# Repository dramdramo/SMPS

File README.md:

# SMPS

Here is the branch where Omar will make changes to the main project

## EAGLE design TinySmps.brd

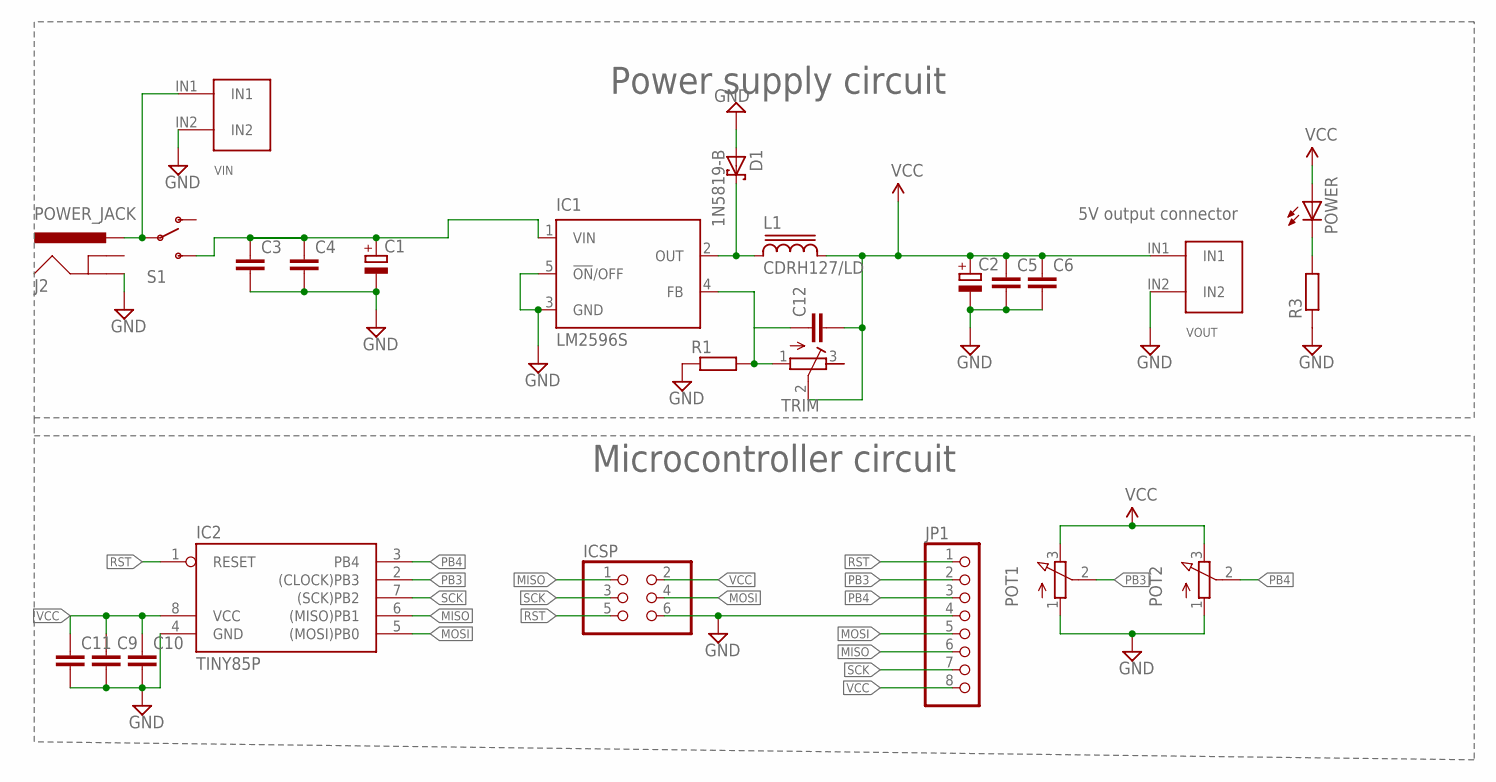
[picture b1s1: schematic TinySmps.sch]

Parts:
C1: CPOL-EUE7.5-16; E7,5-16
C2: CPOL-EUE5-10.5; E5-10,5
C3, C4, C5, C6, C9, C10, C11: C-EUC1206; C1206
C12: C2,5-3; C2.5-3
D1: 1N5819-B; DO41-7.6
IC1: LM2596S; TO263-5
IC2: TINY85P; DIL08
ICSP: PINHD-2X3; 2X03
J2: POWER_JACK; POWER_JACK_PTH
JP1: PINHD-1X8; 1X08
L1: CDRH127/LD
POT1, POT2: 3RP/1610N
POWER: LEDSML0805; SML0805
R1: R-EU_0204/7; 0204/7
R3: R-EU_R1206; R1206
S1: SWITCH-SPDTKIT; SWITCH-SPDT_KIT
TRIM: R-TRIMM3296W; RTRIM3296W
VIN: 1X2_5MM
VOUT: 1X2_5MM

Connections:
GND: C1.-, C2.-, C3.2, C4.2, C5.2, C6.2, C9.2, C10.2, C11.2, D1.A, IC1.3 (GND), IC1.5 (!ON!/OFF), IC2.4 (GND), ICSP.6, J2.GND, JP1.4, POT1.1 (A), POT2.1 (A), R1.1, R3.1, VIN.IN2, VOUT.IN2
IN: C1.+, C3.1, C4.1, IC1.1 (VIN), S1.3 (S)
MISO: IC2.6 ((MISO)PB1), ICSP.1, JP1.6
MOSI: IC2.5 ((MOSI)PB0), ICSP.4, JP1.5
unnamed: POWER.C, R3.2
unnamed: D1.C, IC1.2 (OUT), L1.1
unnamed: C12.1, IC1.4 (FB), R1.2, TRIM.1 (A)
unnamed: J2.PWR, S1.2, VIN.IN1
PB3: IC2.2 ((CLOCK)PB3), JP1.2, POT1.2 (S)
PB4: IC2.3 (PB4), JP1.3, POT2.2 (S)
RST: IC2.1 (RESET), ICSP.5, JP1.1
SCK: IC2.7 ((SCK)PB2), ICSP.3, JP1.7
VCC: C2.+, C5.1, C6.1, C9.1, C10.1, C11.1, C12.2, IC2.8 (VCC), ICSP.2, JP1.8, L1.2, POT1.3 (E), POT2.3 (E), POWER.A, TRIM.2 (S), VOUT.IN1

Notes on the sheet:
Power supply circuit
5V output connector
Microcontroller circuit

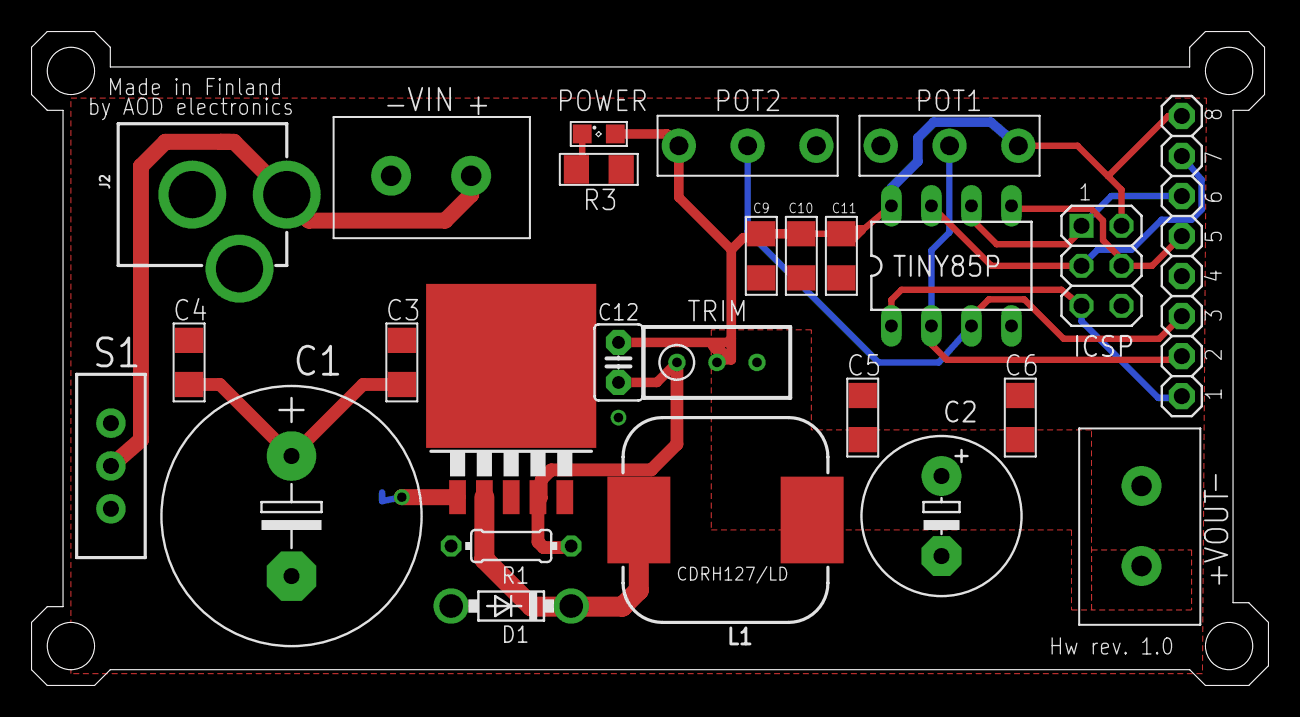
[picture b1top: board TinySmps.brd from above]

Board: 2 copper layers, 78.5 x 41.5 mm, 26 parts (0 on the bottom side), 13 nets.

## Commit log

2017-10-02 Add files via upload
    Changed capacitors, rated for higher input voltage. Added Led status indication for power
2017-10-08 omar changes
2017-10-08 Add files via upload
    omar changes
2017-10-08 Add files via upload
    Changed some bad routes

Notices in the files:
parts and their libraries:
SparkFun-Connectors: Licensing: Creative Commons ShareAlike 4.0 International - https://creativecommons.org/licenses/by-sa/4.0
inductor-sumida: Copyright (C) 2008, Bob Starr
